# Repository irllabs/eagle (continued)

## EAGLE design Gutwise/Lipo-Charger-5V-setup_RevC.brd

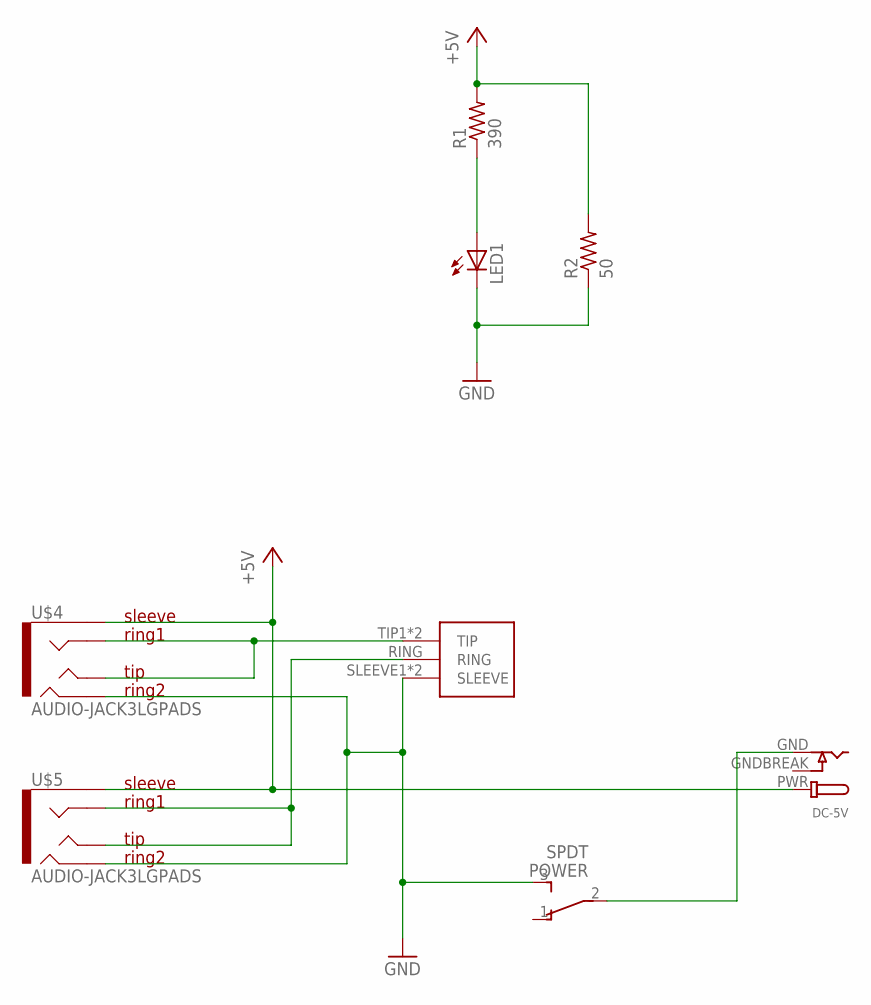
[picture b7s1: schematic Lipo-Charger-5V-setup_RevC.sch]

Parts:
AUDIO_OUT: 1/8"-F-STEREO-PCB
DC-5V: DCBARRELPTH; DCJACK_2MM_PTH
LED1: LED3MM
POWER: SPDT; SWITCH_SPDT-TE-CONNECT
R1: 390; 0204/7
R2: 50; 0204/7
U$4, U$5: AUDIO-JACK3LGPADS; AUDIO-JACK-TRRS-SMD

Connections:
+5V: DC-5V.PWR, R1.2, R2.2, U$4.EARTH, U$5.EARTH
GND: AUDIO_OUT.SLEEVE1 (SLEEVE), AUDIO_OUT.SLEEVE2 (SLEEVE), LED1.K (C), POWER.3, R2.1, U$4.RING2, U$5.RING2
GNDBREAK: DC-5V.GNDBREAK
unnamed: LED1.A, R1.1
unnamed: DC-5V.GND, POWER.2
unnamed: AUDIO_OUT.RING, U$5.RING1, U$5.TIP
OUT2: AUDIO_OUT.TIP1 (TIP), AUDIO_OUT.TIP2 (TIP), U$4.RING1, U$4.TIP

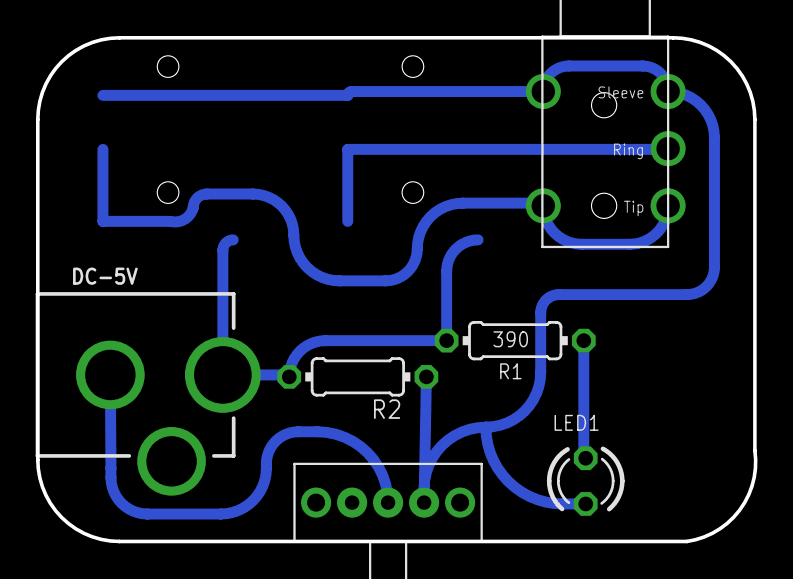
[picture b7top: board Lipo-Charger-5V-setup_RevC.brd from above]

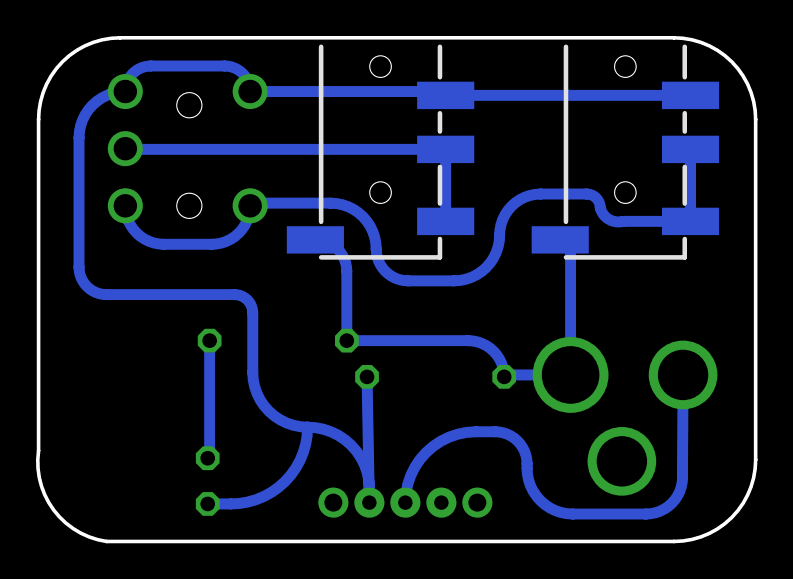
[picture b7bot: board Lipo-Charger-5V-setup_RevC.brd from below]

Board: 2 copper layers, 39.9 x 28.0 mm, 8 parts (2 on the bottom side), 6 nets.
